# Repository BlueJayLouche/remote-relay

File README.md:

# remote-relay

Fire a relay on cue from a lighting or show-control desk over WiFi. An **ESP32-C3**
receives **sACN (E1.31)** or **OSC** and switches a relay on/off — built to trigger
a theatre **aroma diffuser's** air pump, but it's just a network-controlled relay
and works for anything a desk should switch.

Push a fader up / fire a cue → relay closes. Pull it down, or lose the network →
relay opens. Failsafes force it **off** on WiFi loss, on a 2.5 s sACN stream gap,
and after an optional Max-ON timeout.

## Quick start

```bash
pio run -e c3 -t upload      # compile + flash over USB-C
pio device monitor           # watch logs (115200)
```

1. Join the setup WiFi **`AromaDiffuser-setup`** (password `aroma1234`), browse to
   **`http://192.168.4.1/`**, and set your show network + protocol/addresses.
2. Once on your network, it's at **`http://aroma.local/`** — live status, a **Test
   puff** button, and a **Config** page to change protocol, universe/channel,
   hostname, etc. without re-flashing.

## Details

- **[IMPLEMENTATION.md](IMPLEMENTATION.md)** — wiring, bill of materials, safety,
  configuration, bench-testing, and behaviour reference.
- **[ESP32_Relay/](ESP32_Relay/README.md)** — the custom carrier PCB (KiCad).

Target: ESP32-C3 Super Mini · PlatformIO env `c3` · arduino-esp32 v3 (pioarduino).

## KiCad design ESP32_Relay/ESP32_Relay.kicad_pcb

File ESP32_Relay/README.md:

# ESP32_Relay — AromaDiffuser carrier board

A basic 2-layer carrier PCB for the [AromaDiffuser](../IMPLEMENTATION.md) controller:
**12 V in → buck → ESP32-C3 Super Mini → transistor → relay → pump out.**

~80 × 60 mm, 2-layer, **fully routed** with a GND pour. The relay is a dry SPDT
contact, so the switched side works for an **AC or DC** pump (subject to the mains
caveat below).

## How it was generated

Three scripts, run in order with KiCad's bundled Python. KiCad has no schematic
Python API, so each `.kicad_*` is written directly; the schematic and PCB are kept
consistent by sharing the same net names.

```bash
KPY=/Applications/KiCad/KiCad.app/Contents/Frameworks/Python.framework/Versions/Current/bin/python3
$KPY gen_board.py    # footprints, nets, GND pour, outline, mounting holes
$KPY gen_sch.py      # matching schematic (symbols + net labels)
$KPY gen_routes.py   # route the 6 non-GND nets
```

Verified with `kicad-cli`: schematic **ERC clean**, PCB **DRC clean (0 violations,
0 unrouted)**, and the schematic netlist matches the PCB. See `schematic.pdf`.

> The PCB carries its own netlist (no sheet-to-board link). If you edit the
> schematic and want to push changes, re-run `gen_routes.py` rather than KiCad's
> "Update PCB from schematic".

## ⚠️ Before you fabricate — verify these

It's DRC/ERC-clean, but still **bench-verify** the part-specific assumptions:

1. **C3 header pitch.** `A1`/`A2` are 2× 1×8 headers, rows **13 mm** apart. "Super
   Mini" clones vary — measure yours and adjust the `A1`/`A2` X positions in
   `gen_board.py` if needed before fab.
2. **Relay pinout.** Wired to the KiCad **SANYOU SRD** map (derived from the symbol):
   pin 1 = COM, pin 3 = NO, pins 2 & 5 = coil, pin 4 = NC (unused). Confirm your
   relay matches (SRD-05VDC-SL-C does).
3. **Transistor pinout.** Laid out for **PN2222A** in TO-92, pads 1-2-3 = **E-B-C**.
   A BC547 is C-B-E — different. Match the part to the footprint or you'll cook it.
4. **Mains pump = STOP.** This board's spacing (2.54 mm / 5 mm) is for a **low-voltage
   DC pump only**. If your pump is **AC mains**, do *not* run mains on this board —
   keep the mains switching on a separately mains-rated relay module off-board, or
   redesign for proper creepage/clearance + fusing + enclosure. (We still haven't
   measured the pump — do that first; see IMPLEMENTATION.md.)
5. **Buck.** `U1` is an **MP1584 module** on a 1×4 header — set its trimmer to **5.0 V
   before** connecting the C3.

## Netlist (matches `schematic.pdf` and the PCB)

| Net | Connections |
|-----|-------------|
| **+12V** | J1.1 (12V IN), U1.1 (buck VIN+), K1.1 (relay COM) |
| **+5V** | U1.3 (buck VOUT+), A1.1 (C3 5V), K1.2 (coil+), D1.1 (diode K) |
| **GND** | J1.2, U1.2, U1.4, A1.2 (C3 GND), Q1.1 (emitter), R2.2, J2.2, H1–H4, pour |
| **CTRL_IO10** | A2.6 (C3 GPIO10), R1.1, R2.1 |
| **Q_BASE** | R1.2, Q1.2 (base) |
| **COIL_DRV** | Q1.3 (collector), K1.5 (coil−), D1.2 (diode A) |
| **PUMP** | K1.3 (relay NO), J2.1 |

`R2` (10 k, GPIO10→GND) holds the transistor off during boot/reset → **pump off at
power-up**. `D1` is the coil flyback (band/cathode to +5 V).

## BOM

| Ref | Part | Notes |
|-----|------|-------|
| A1, A2 | 2× 1×8 socket header, 2.54 mm | seat the ESP32-C3 Super Mini |
| U1 | MP1584 buck module + 1×4 header | 12 V → **5.0 V** |
| K1 | SPDT relay, 5 V coil | SRD-05VDC-SL-C (or pin-compatible) |
| Q1 | NPN BJT, TO-92 | PN2222A (E-B-C) |
| D1 | diode, DO-41 | 1N4007 |
| R1 | resistor | 1 kΩ (base) |
| R2 | resistor | 10 kΩ (pulldown) |
| J1, J2 | 2-pin screw terminal, 5 mm | J1 = 12V IN, J2 = PUMP |
| H1–H4 | M3 mounting holes | grounded |

## Fab

Export gerbers:

```bash
/Applications/KiCad/KiCad.app/Contents/MacOS/kicad-cli pcb export gerbers --output gerbers/ ESP32_Relay.kicad_pcb
/Applications/KiCad/KiCad.app/Contents/MacOS/kicad-cli pcb export drill   --output gerbers/ ESP32_Relay.kicad_pcb
```

…or just upload `ESP32_Relay.kicad_pcb` directly to JLCPCB/PCBWay.

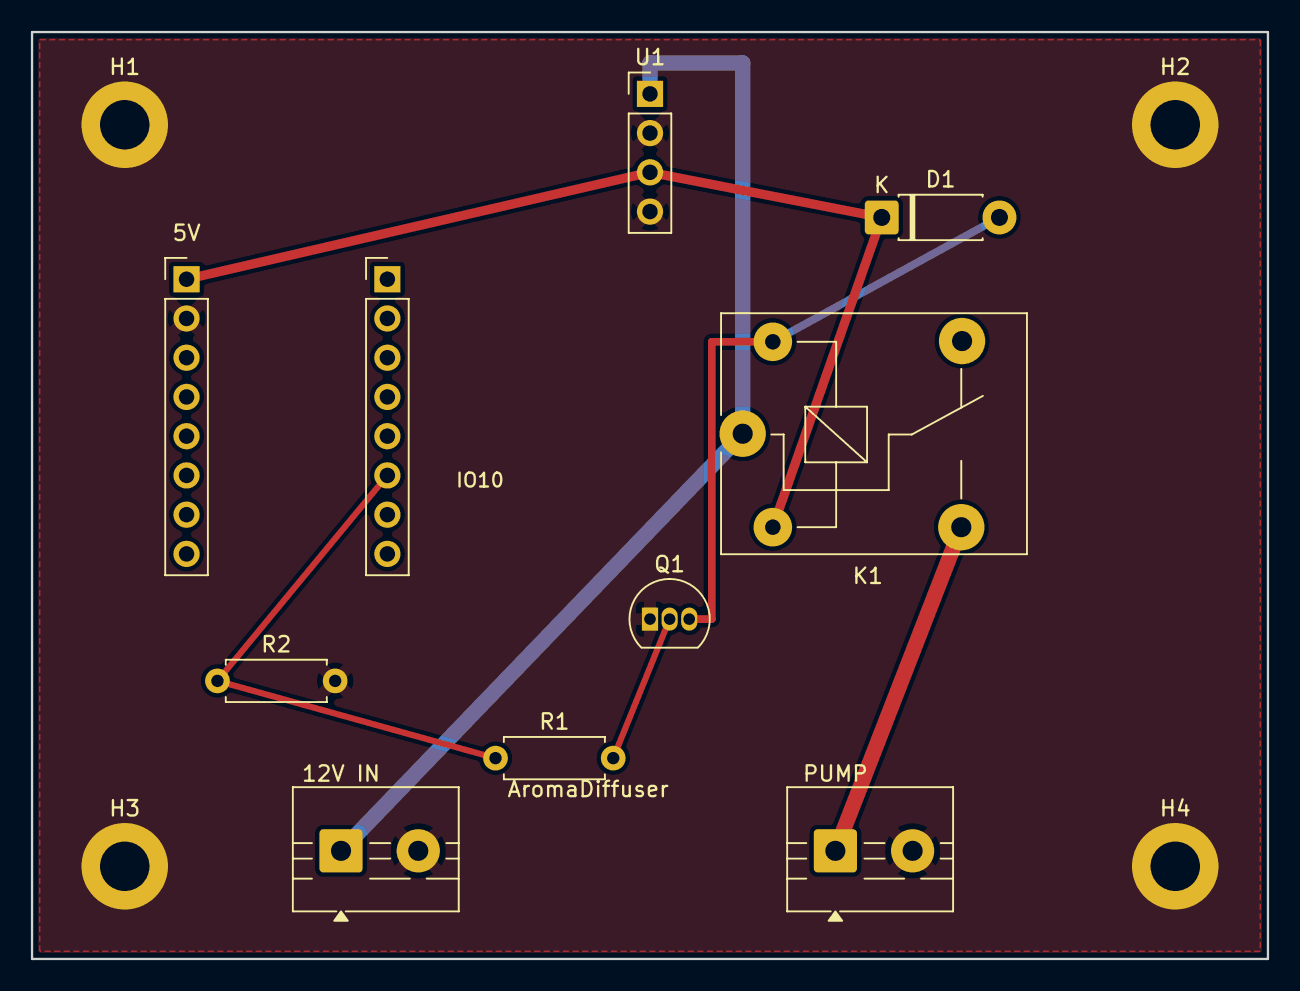
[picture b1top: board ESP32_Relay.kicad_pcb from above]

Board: 2 copper layers, 80.0 x 60.0 mm, 14 parts (0 on the bottom side), 7 nets.

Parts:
A1: C3 L:5V,GND,3V3,IO4,IO3,IO2,IO1,IO0; PinHeader_1x08_P2.54mm_Vertical
A2: C3 R:IO5,IO6,IO7,IO8,IO9,IO10,RX,TX; PinHeader_1x08_P2.54mm_Vertical
D1: 1N4007 (band=K -> +5V); D_DO-41_SOD81_P7.62mm_Horizontal
H1, H2, H3, H4: MountingHole_3.2mm_M3_DIN965_Pad
J1: 12V IN; TerminalBlock_MaiXu_MX126-5.0-02P_1x02_P5.00mm
J2: PUMP; TerminalBlock_MaiXu_MX126-5.0-02P_1x02_P5.00mm
K1: 5V relay SRD-05VDC-SL-C; Relay_SPDT_SANYOU_SRD_Series_Form_C
Q1: PN2222A E-B-C; TO-92_Inline
R1: 1k base; R_Axial_DIN0207_L6.3mm_D2.5mm_P7.62mm_Horizontal
R2: 10k pulldown; R_Axial_DIN0207_L6.3mm_D2.5mm_P7.62mm_Horizontal
U1: MP1584 12V->5V: VIN+,VIN-,VOUT+,VOUT-; PinHeader_1x04_P2.54mm_Vertical

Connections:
+5V: A1.1, D1.1, K1.2, U1.3
+12V: J1.1, K1.1, U1.1
COIL_DRV: D1.2, K1.5, Q1.3
CTRL_IO10: A2.6, R1.1, R2.1
GND: A1.2, H1.1, H2.1, H3.1, H4.1, J1.2, J2.2, Q1.1, R2.2, U1.2, U1.4
PUMP: J2.1, K1.3
Q_BASE: Q1.2, R1.2
